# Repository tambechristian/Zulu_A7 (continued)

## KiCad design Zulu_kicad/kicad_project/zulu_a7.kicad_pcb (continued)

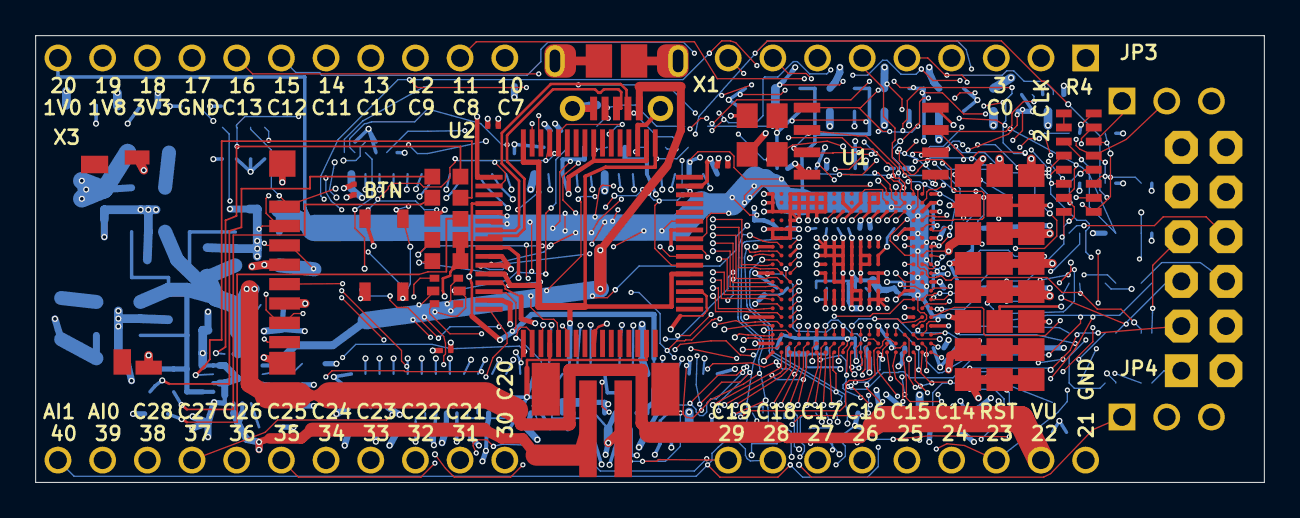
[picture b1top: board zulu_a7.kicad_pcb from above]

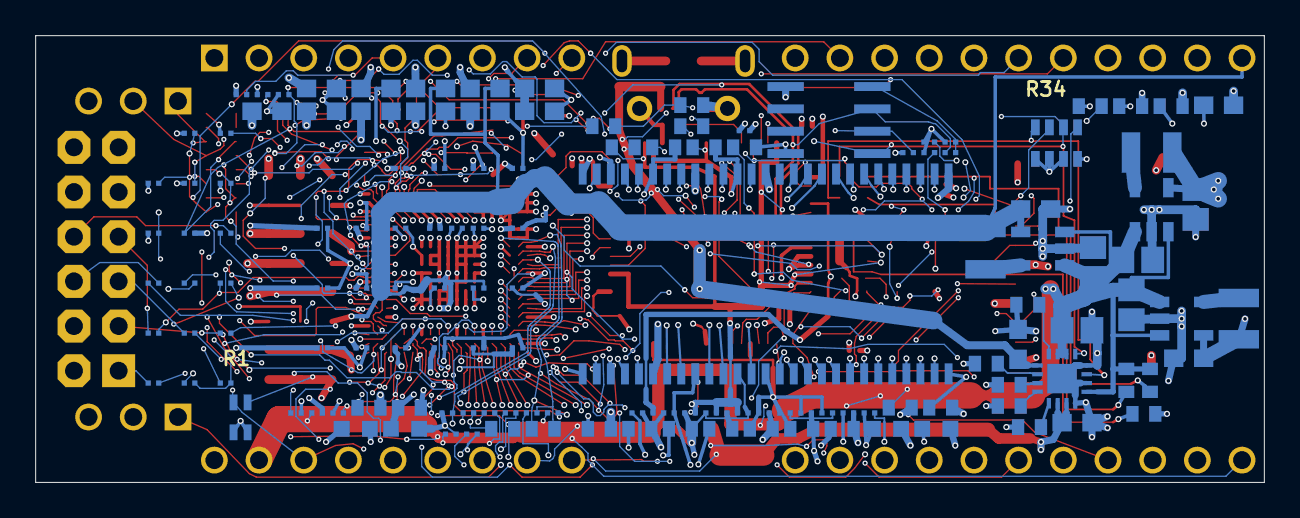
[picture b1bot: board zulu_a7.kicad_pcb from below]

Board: 6 copper layers, 69.8 x 25.4 mm, 178 parts (139 on the bottom side), 177 nets.

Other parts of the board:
C123: 100nF; C0201
C124: 470nF; C0402
L6, L7: FB 600R; IND0603
R20, R22, R23: 1K; R0201
R21: 1K; R0402

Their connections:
CFG-M0: R20.1; also elsewhere on the board
CFG-M1: R21.2; also elsewhere on the board
CFG-M2: R22.2; also elsewhere on the board
GND: L6.1, R21.1, R22.1; also elsewhere on the board
GNDADC: C123.2, C124.2, L6.2; also elsewhere on the board
PUDC_B: R23.2; also elsewhere on the board
VCC1V8: L7.1; also elsewhere on the board
VCC3V3: R20.2, R23.1; also elsewhere on the board
VCCADC: C123.1, C124.1, L7.2; also elsewhere on the board

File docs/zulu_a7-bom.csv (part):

Item,Qty,Refdes,Value,Package,Manufacturer,MANF#,Spec,Fitted,Note
1,1,J1,Pmod 2x6,2X06,Sullins,PPTC062LFBN-RC,"2x6 female header, 2.54 mm pitch, through-hole, 12 way -- Pmod host socket",yes,"A SOCKET, NOT PINS, AND THE LIBRARY NAME DISAGREES WITH THAT. The package is called PIN HEADER 2x6 and the deviceset PINHD-2X6, which is inherited naming, but on a Digilent Pmod the HOST carries the female socket and the peripheral module carries the male pins that plug into it. Cmod A7 is the same. Order male pins off that library name and no Pmod will mate. The footprint is 12 plated holes on 2.54 either way, so a male header such as Sullins PRPC006DAAN-RC drops into the same land if you would rather have pins and a cable. Height 8.5 mm is not a problem: J1 is on the FRONT, and it is the back that faces a breadboard a couple of millimetres away."
2,1,Q1,12MHz 10ppm (FPGA + FT2232HL),32X25,ECS,ECS-3225SMV-120-FP-TR,"12.000 MHz HCMOS XO, 1.62-3.63 V, +-10 ppm incl. initial, temp -40..105 C, supply, load, reflow and aging (ECS-3225SMV sheet p1), 3.2x2.5x1.2 mm, pin 1 tri-state (H/NC = run), 6 mA typ / 10 mA max; replaced the +-50 ppm ASEM1-12.000MHZ-LC-T on 2026-09-08",yes,"ACTIVE OSCILLATOR, NOT A CRYSTAL -- the schematic settles it: pin 2 to GND, pin 4 to VCC3V3, pin 3 out into R24 and R25, and pin 1 tied to VCC3V3, which is a 4-pad XO with its enable held high. A crystal would have two pads and load capacitors. THE FREQUENCY IS NOT A CHOICE: the FT2232H wants 12 MHz for its USB PLL, so that was fixed before anything else. 25 ppm is the value already recorded and is comfortably inside what FTDI asks of the reference. Output drives two loads through 33R each, the FT2232's OSCI and the FPGA clock ball. Pin 1 to Vdd suits either an OE part or one with pin 1 not connected, so the choice is not narrowed by it. ASEM1 is the family the design note already named. Confirm the suffix -- it encodes stability and temperature range and is the easy thing to get wrong."
3,1,R1,4.7K,742C043,CTS,742C043472JP,"2 x 4.7K +-5% isolated array, 0606 concave 1.60 x 1.60 mm, 0.80 mm pitch, 63 mW per element",yes,"The two configuration pull-ups in one package: A on INIT_B (net FPGA-INIT#), B on PROGRAM_B (net RST#). Both commons are pads 3 and 4, side by side on one long side of the body, and both go to VCC3V3. CTS publishes ONE recommended land pattern for the whole 742 package family, so this footprint is the 742C083 pad cell already validated for R34 with two pads per side instead of four. 5 percent: the 742C043 has no 1 percent option either, and a configuration pull-up does not care; 63 mW per element against the 2.3 mW that 3.3 V across 4.7 k actually dissipates. Alternate on the identical land: Panasonic EXB-V4V472JV, same 1.60 x 1.60 mm concave body on 0.80 mm pitch. Do NOT substitute EXB-34V472JV -- same size, convex terminals, different land. R99, the third 4.7 k pull-up on this sheet, stays discrete: it sits on PROG#, the far side of the 100 ohm now in R4. TOLERANCE AGAINST UG470: Table 2-4 asks for a pull-up of 4.7 kohm OR LESS on both of these pins, and this is a 5 percent part, so its worst case is 4.935 k -- 5 percent outside the stated maximum. That is a wording problem rather than a physical one. The limit exists to hold the pin high against input leakage, and DS181 worst-case leakage of 15 uA across 4.935 k is 74 mV, against a VIH of 2.0 V. The discretes this replaces were 1 percent parts and were already outside the same limit, at 4.747 k. Strict compliance would mean 4.3 kohm +-5 percent (4.515 k worst case), but CTS does not stock a 432 code in the 742C043 family -- the stocked spread is 101, 220, 470, 471, 472, 473, 102, 103 and 104 -- so buying compliance here would cost availability, which is the thing that actually stops a board getting built. Dropping to the next stocked value, 1 k, would cost margin where it matters: it lifts the low level the bridge can assert on RST# through the 100 ohm from 0.10 V to 0.43 V."
4,1,R34,4.7K,742C083,CTS,742C083472JP,"4x4.7K isolated array 0603x4, 0.8 mm pitch; direct successor of the obsolete JTR",yes,"The microSD DAT0-3 pull-ups, all four elements used -- which is what an array is actually for. R1, R2 and R4 used 2, 3 and 6 of theirs in the EAGLE original and were split into discretes during the import; on 2026-09-09 R1 and R4 went back into arrays of their own (742C043472JP and 742C163101JP), so all three arrays on this board are CTS 74x concave parts sharing one land-pattern rule. R2 is still a discrete. 4.7k is the conventional value for SD data lines and it was already chosen; only the part number was missing. 5 percent is ample for a pull-up, so this is a J part where the discrete resistors on this board are F. CTS 742C is the family the footprint is named after. Confirm the suffix -- it encodes tolerance and packaging and is the easy thing to get wrong."
5,1,R4,100,742C163,CTS,742C163101JP,"8 x 100 ohm +-5% isolated array, 2506 concave 6.40 x 1.60 mm, 0.80 mm pitch, 63 mW per element; six elements used, two spare",yes,"The six 100 ohm series resistors between the FT2232H and the FPGA in one package: A PROG#, B DONE, C TDI, D TDO, E TMS, F TCK, in the order they are drawn down the sheet. Pads 1-6 face the bridge and pads 16-11 face the FPGA, one long side of the body per end of the link. TWO ELEMENTS ARE SPARE (pads 7-10); they sit at the far end of the body, so the six used run contiguously from pad 1. Leave the spare pads unconnected. There is no purchasable 6-element part: CTS 753123101GP is a genuine 12-terminal, 6-isolated-element, 100 ohm array, but Digi-Key holds none, quotes 28 weeks at MOQ 1000 and $2.63 each, and its 12-SRT body is 8.76 x 2.03 mm, LARGER than this 8-element chip array. Same CTS 74x concave family as R34, so all three arrays on the board answer to one CTS land-pattern rule (0.45 x 0.80 mm pads, 0.80 mm pitch, 2.60 mm across). 5 percent like R34: the 742C163 has no 1 percent option, which series damping does not care about, and 63 mW per element is twenty times the worst case. Alternate if the layout needs the length back: Panasonic EXB-2HV101JV is the same 8 x 100 ohm isolated in 3.80 x 1.60 mm, but convex terminals on 0.50 mm pitch, so it needs its own land pattern. AT LAYOUT: all six lines now converge on one part -- put it between the bridge and the FPGA where the four JTAG lines already run together, and keep TCK, element F on pads 6/11, at the end of the body: its only live neighbour is TMS. SUPPLY CAVEATS, all read 2026-09-09. (1) CTS files the whole 74x series -- this part and R34's 742C083 with it -- under Legacy Products on its own site. Near-term risk is low: 25,352 stocked, MOQ 1, deep sibling stock. It is not a young family. (2) There is no drop-in second source on this land. The alternate above needs its own footprint, so this one package is a single point of failure where the six discretes it replaces had many interchangeable vendors; if that matters for the build, qualify a second 16-pad 0.80 mm concave array on the same land first. (3) Every stock and price figure here is Digi-Key alone -- Mouser, Arrow, TTI, Octopart and LCSC all refused automated reads that day -- so none of it has second-distributor corroboration. AND ONE LAYOUT POINT: the two spare elements are unplaced, so pads 7-10 carry no net. If the layout wants them as grounded metal beside TCK, that has to come back here as two more placed gates with both ends on GND; it cannot be done in the PCB alone."
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
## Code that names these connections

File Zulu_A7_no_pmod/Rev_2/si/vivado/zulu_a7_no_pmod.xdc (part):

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set_property -dict {PACKAGE_PIN N2   IOSTANDARD LVCMOS33} [get_ports {A9}]  ;# A9  bank 35  IO_L10P_T1_AD15P_35
set_property -dict {PACKAGE_PIN V2   IOSTANDARD LVCMOS33} [get_ports {BS0}]  ;# BS0  bank 34  IO_L5P_T0_34
set_property -dict {PACKAGE_PIN U1   IOSTANDARD LVCMOS33} [get_ports {BS1}]  ;# BS1  bank 34  IO_L3N_T0_DQS_34
set_property -dict {PACKAGE_PIN N19  IOSTANDARD LVCMOS33} [get_ports {BTN}]  ;# BTN  bank 14  IO_L9N_T1_DQS_D13_14
set_property -dict {PACKAGE_PIN W3   IOSTANDARD LVCMOS33} [get_ports {CAS_N}]  ;# CAS#  bank 34  IO_L6N_T0_VREF_34
set_property -dict {PACKAGE_PIN B18  IOSTANDARD LVCMOS33} [get_ports {CHAN0}]  ;# CHAN0  bank 16  IO_L19P_T3_16
set_property -dict {PACKAGE_PIN A18  IOSTANDARD LVCMOS33} [get_ports {CHAN1}]  ;# CHAN1  bank 16  IO_L19N_T3_VREF_16
set_property -dict {PACKAGE_PIN J19  IOSTANDARD LVCMOS33} [get_ports {CHAN10}]  ;# CHAN10  bank 14  IO_L6N_T0_D08_VREF_14
set_property -dict {PACKAGE_PIN K18  IOSTANDARD LVCMOS33} [get_ports {CHAN11}]  ;# CHAN11  bank 14  IO_L8N_T1_D12_14
set_property -dict {PACKAGE_PIN E19  IOSTANDARD LVCMOS33} [get_ports {CHAN12}]  ;# CHAN12  bank 14  IO_L3N_T0_DQS_EMCCLK_14
set_property -dict {PACKAGE_PIN H19  IOSTANDARD LVCMOS33} [get_ports {CHAN13}]  ;# CHAN13  bank 14  IO_L4P_T0_D04_14
set_property -dict {PACKAGE_PIN W17  IOSTANDARD LVCMOS33} [get_ports {CHAN14}]  ;# CHAN14  bank 14  IO_L20N_T3_A07_D23_14
set_property -dict {PACKAGE_PIN V17  IOSTANDARD LVCMOS33} [get_ports {CHAN15}]  ;# CHAN15  bank 14  IO_L19N_T3_A09_D25_VREF_14
set_property -dict {PACKAGE_PIN W16  IOSTANDARD LVCMOS33} [get_ports {CHAN16}]  ;# CHAN16  bank 14  IO_L20P_T3_A08_D24_14
set_property -dict {PACKAGE_PIN U16  IOSTANDARD LVCMOS33} [get_ports {CHAN17}]  ;# CHAN17  bank 14  IO_L23N_T3_A02_D18_14
set_property -dict {PACKAGE_PIN V16  IOSTANDARD LVCMOS33} [get_ports {CHAN18}]  ;# CHAN18  bank 14  IO_L19P_T3_A10_D26_14
set_property -dict {PACKAGE_PIN W15  IOSTANDARD LVCMOS33} [get_ports {CHAN19}]  ;# CHAN19  bank 14  IO_L21N_T3_DQS_A06_D22_14
set_property -dict {PACKAGE_PIN B17  IOSTANDARD LVCMOS33} [get_ports {CHAN2}]  ;# CHAN2  bank 16  IO_L14N_T2_SRCC_16
set_property -dict {PACKAGE_PIN V15  IOSTANDARD LVCMOS33} [get_ports {CHAN20}]  ;# CHAN20  bank 14  IO_L21P_T3_DQS_14
set_property -dict {PACKAGE_PIN U15  IOSTANDARD LVCMOS33} [get_ports {CHAN21}]  ;# CHAN21  bank 14  IO_L23P_T3_A03_D19_14
set_property -dict {PACKAGE_PIN W14  IOSTANDARD LVCMOS33} [get_ports {CHAN22}]  ;# CHAN22  bank 14  IO_L22N_T3_A04_D20_14
set_property -dict {PACKAGE_PIN V14  IOSTANDARD LVCMOS33} [get_ports {CHAN23}]  ;# CHAN23  bank 14  IO_L24N_T3_A00_D16_14
set_property -dict {PACKAGE_PIN U14  IOSTANDARD LVCMOS33} [get_ports {CHAN24}]  ;# CHAN24  bank 14  IO_25_14
set_property -dict {PACKAGE_PIN W13  IOSTANDARD LVCMOS33} [get_ports {CHAN25}]  ;# CHAN25  bank 14  IO_L22P_T3_A05_D21_14
set_property -dict {PACKAGE_PIN V13  IOSTANDARD LVCMOS33} [get_ports {CHAN26}]  ;# CHAN26  bank 14  IO_L24P_T3_A01_D17_14
set_property -dict {PACKAGE_PIN T18  IOSTANDARD LVCMOS33} [get_ports {CHAN27}]  ;# CHAN27  bank 14  IO_L17N_T2_A13_D29_14
set_property -dict {PACKAGE_PIN T17  IOSTANDARD LVCMOS33} [get_ports {CHAN28}]  ;# CHAN28  bank 14  IO_L17P_T2_A14_D30_14
set_property -dict {PACKAGE_PIN A17  IOSTANDARD LVCMOS33} [get_ports {CHAN3}]  ;# CHAN3  bank 16  IO_L12N_T1_MRCC_16
set_property -dict {PACKAGE_PIN C16  IOSTANDARD LVCMOS33} [get_ports {CHAN4}]  ;# CHAN4  bank 16  IO_L13P_T2_MRCC_16
set_property -dict {PACKAGE_PIN D17  IOSTANDARD LVCMOS33} [get_ports {CHAN5}]  ;# CHAN5  bank 14  IO_0_14
set_property -dict {PACKAGE_PIN H17  IOSTANDARD LVCMOS33} [get_ports {CHAN6}]  ;# CHAN6  bank 14  IO_L5P_T0_D06_14
set_property -dict {PACKAGE_PIN G17  IOSTANDARD LVCMOS33} [get_ports {CHAN7}]  ;# CHAN7  bank 14  IO_L5N_T0_D07_14
set_property -dict {PACKAGE_PIN J18  IOSTANDARD LVCMOS33} [get_ports {CHAN8}]  ;# CHAN8  bank 14  IO_L7N_T1_D10_14
set_property -dict {PACKAGE_PIN J17  IOSTANDARD LVCMOS33} [get_ports {CHAN9}]  ;# CHAN9  bank 14  IO_L7P_T1_D09_14
set_property -dict {PACKAGE_PIN P18  IOSTANDARD LVCMOS33} [get_ports {CHAN_CLK}]  ;# CHAN-CLK  bank 14  IO_L14P_T2_SRCC_14
set_property -dict {PACKAGE_PIN M2   IOSTANDARD LVCMOS33} [get_ports {CKE}]  ;# CKE  bank 35  IO_L9P_T1_DQS_AD7P_35
set_property -dict {PACKAGE_PIN L17  IOSTANDARD LVCMOS33} [get_ports {CLK_12M_FPGA}]  ;# CLK-12M-FPGA  bank 14  IO_L12P_T1_MRCC_14
set_property -dict {PACKAGE_PIN V8   IOSTANDARD LVCMOS33} [get_ports {D0}]  ;# D0  bank 34  IO_L14N_T2_SRCC_34
set_property -dict {PACKAGE_PIN V7   IOSTANDARD LVCMOS33} [get_ports {D1}]  ;# D1  bank 34  IO_L19N_T3_VREF_34
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set_property -dict {PACKAGE_PIN G18  IOSTANDARD LVCMOS33} [get_ports {FLASH_D02}]  ;# FLASH-D02  bank 14  IO_L2P_T0_D02_14
set_property -dict {PACKAGE_PIN F18  IOSTANDARD LVCMOS33} [get_ports {FLASH_D03}]  ;# FLASH-D03  bank 14  IO_L2N_T0_D03_14
set_property -dict {PACKAGE_PIN P19  IOSTANDARD LVCMOS33} [get_ports {FT_PWREN_N}]  ;# FT-PWREN#  bank 14  IO_L10P_T1_D14_14
set_property -dict {PACKAGE_PIN W4   IOSTANDARD LVCMOS33} [get_ports {LDQM}]  ;# LDQM  bank 34  IO_L12N_T1_MRCC_34
set_property -dict {PACKAGE_PIN N17  IOSTANDARD LVCMOS33} [get_ports {LED0_B}]  ;# LED0_B  bank 14  IO_L13P_T2_MRCC_14
set_property -dict {PACKAGE_PIN R18  IOSTANDARD LVCMOS33} [get_ports {LED0_G}]  ;# LED0_G  bank 14  IO_L14N_T2_SRCC_14
set_property -dict {PACKAGE_PIN P17  IOSTANDARD LVCMOS33} [get_ports {LED0_R}]  ;# LED0_R  bank 14  IO_L13N_T2_MRCC_14
set_property -dict {PACKAGE_PIN N18  IOSTANDARD LVCMOS33} [get_ports {LED1}]  ;# LED1  bank 14  IO_L9P_T1_DQS_14
set_property -dict {PACKAGE_PIN M19  IOSTANDARD LVCMOS33} [get_ports {LED2}]  ;# LED2  bank 14  IO_L11N_T1_SRCC_14
set_property -dict {PACKAGE_PIN V3   IOSTANDARD LVCMOS33} [get_ports {RAS_N}]  ;# RAS#  bank 34  IO_L6P_T0_34
set_property -dict {PACKAGE_PIN M1   IOSTANDARD LVCMOS33} [get_ports {SDRAM_CLK}]  ;# SDRAM-CLK  bank 35  IO_L9N_T1_DQS_AD7N_35
set_property -dict {PACKAGE_PIN W2   IOSTANDARD LVCMOS33} [get_ports {SDRAM_CS_N}]  ;# SDRAM-CS#  bank 34  IO_L5N_T0_34
set_property -dict {PACKAGE_PIN U8   IOSTANDARD LVCMOS33} [get_ports {SD_CLK}]  ;# SD-CLK  bank 34  IO_L14P_T2_SRCC_34
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set_property -dict {PACKAGE_PIN B15  IOSTANDARD LVCMOS33} [get_ports {SD_DAT1}]  ;# SD-DAT1  bank 16  IO_L11N_T1_SRCC_16
set_property -dict {PACKAGE_PIN L3   IOSTANDARD LVCMOS33} [get_ports {SD_DAT2}]  ;# SD-DAT2  bank 35  IO_L8P_T1_AD14P_35
set_property -dict {PACKAGE_PIN A16  IOSTANDARD LVCMOS33} [get_ports {SD_DAT3}]  ;# SD-DAT3  bank 16  IO_L12P_T1_MRCC_16
set_property -dict {PACKAGE_PIN B16  IOSTANDARD LVCMOS33} [get_ports {UART_FT_CTS_N}]  ;# UART_FT_CTS#  bank 16  IO_L13N_T2_MRCC_16
set_property -dict {PACKAGE_PIN M18  IOSTANDARD LVCMOS33} [get_ports {UART_FT_DTR_N}]  ;# UART_FT_DTR#  bank 14  IO_L11P_T1_SRCC_14
set_property -dict {PACKAGE_PIN L18  IOSTANDARD LVCMOS33} [get_ports {UART_FT_RTS_N}]  ;# UART_FT_RTS#  bank 14  IO_L8P_T1_D11_14
set_property -dict {PACKAGE_PIN G19  IOSTANDARD LVCMOS33} [get_ports {UART_FT_RXD}]  ;# UART_FT_RXD  bank 14  IO_L4N_T0_D05_14
set_property -dict {PACKAGE_PIN K17  IOSTANDARD LVCMOS33} [get_ports {UART_FT_TXD}]  ;# UART_FT_TXD  bank 14  IO_L12N_T1_MRCC_14
set_property -dict {PACKAGE_PIN L2   IOSTANDARD LVCMOS33} [get_ports {UDQM}]  ;# UDQM  bank 35  IO_L5N_T0_AD13N_35
set_property -dict {PACKAGE_PIN V4   IOSTANDARD LVCMOS33} [get_ports {WE_N}]  ;# WE#  bank 34  IO_L11N_T1_SRCC_34

# ---- SDRAM bus drive strength, 2026-09-15 -----------------------------------------------
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
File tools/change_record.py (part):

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        ("", "Triple synchronous buck. Replaces the two LDOs rev1 proposed and the two the original board had &mdash; one part now makes 1.0 V, 1.8 V and 3.3 V")),
    row(("mono", "BTN1"), ("old mono", "PTA-142 + R87, R88"), ("arrow", "−"), ("mono", "deleted"),
        ("", "Removed to buy back board area &mdash; the button, its 10 k series resistor and its 10 k pull-down. "
             "Frees ball B18, which is now CHAN28 on header pin 41 &mdash; see §7. BTN is untouched")),
    row(("mono", "U10"), ("old", "— new —"), ("arrow", "＋"), ("mono", VAL["U10"]),
        ("", "FTDI reference-design EEPROM, carries the USB VID/PID/product string. <strong>16 bits wide</strong> "
             "&mdash; the <span class='mono'>B</span> suffix &mdash; because DS_FT2232H p27 requires it; see §3")),
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        <thead><tr><th>Pin</th><th>Pad</th><th>MPSSE role</th><th>Net</th></tr></thead>
        <tbody>__CHA__</tbody></table></div>
      <p class="note">TCK/TDI/TDO/TMS are series-terminated through R89-R92 and shared with header JP3 and the R4 pack.
      GPIOL0/GPIOL1 carry <span class="mono">PROG#</span> and <span class="mono">DONE</span>, so the host can already
      force a reconfiguration and read back DONE without spending an FPGA general I/O.</p>
    </div>
    <div>
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    34.29, between CHAN3 and CHAN4. 10.16&nbsp;mm centre-to-centre, 8.64&nbsp;mm clear against X1's 7.80&nbsp;mm of
    copper and 7.50&nbsp;mm of body, so it clears both neighbours by 0.42&nbsp;mm. On the board that is
    <span class="mono">X1 at (22.90, 13.97) rot R90</span>, opening facing the x=25.40 edge.</li>
    <li><strong>Every pin keeps the signal it had.</strong> Pin 2 is still CHAN0, pin 5 still CHAN3, pin 6 still
    CHAN4, pin 13 still CHAN11 — the gate-to-pad map did not change. Only pads 2-5 moved, each +7.62&nbsp;mm into the
    space the gap had been occupying; pads 1 and 6-18 did not move at all.</li>
    <li><strong>The bottom row was closed up and is contiguous</strong> — pins 19..37 from x=49.53 down to x=3.81, and
    the empty position is the board corner at x=1.27. Getting there <strong>moved three pins</strong> 2.54 mm:
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    <li><strong>The gap is reserved, not spare.</strong> It is kept clear for the edge-mounted micro-USB. As drawn, X1
    needs 2.60 mm for its contacts and about 7.8 mm for its shell against 6.10 mm of clear space, so the board edge has
    to move out or a third position has to go before it drops in.</li>
    <li>Channels are now <span class="mono">CHAN0..CHAN27</span> on pins 2-13 and 19-34, contiguous. The old numbering
    ran 0-13 then 15-31 — there was never a CHAN14. GND is pin 16, and it is the only ground pin.</li>
    <li><strong>The board is now 0.800 &times; 2.750 in &mdash; 20.32 &times; 69.85&nbsp;mm &mdash; and sized to a
    breadboard.</strong> X2's two rows were 0.900&nbsp;in apart, which is columns B and I and leaves one free column
    each side. They are now <strong>0.700&nbsp;in</strong> apart: columns <strong>C and H</strong>, with A, B, I and J
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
